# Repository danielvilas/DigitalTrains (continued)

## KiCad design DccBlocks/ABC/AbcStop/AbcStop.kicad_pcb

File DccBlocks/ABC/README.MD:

# ABC Stop Signal Generator
Generator of Lenz's async signal to stop a loco

Subprojects
* __[AbcSimulation](AbcSimulation)__:Simulation Circuits to Test
* __[AbcStop](AbcStop)__: Stop Circuit generator with Mosfet ByPass
* __[AbcTestBoard](AbcTestBoard)__: Test Board for the checking the Mosfets circuits

## TODO
- Hardware
  - [x] Join Test and Stop
  - [] Diode Documentation
  - [] Add a DCC decoder
  - [] DCC self Powered (from DCC)
  - [] Version no Opto
- Software
  - [] On/Off
  - [] Slow?
  - [] Study PIC, RP2040,...

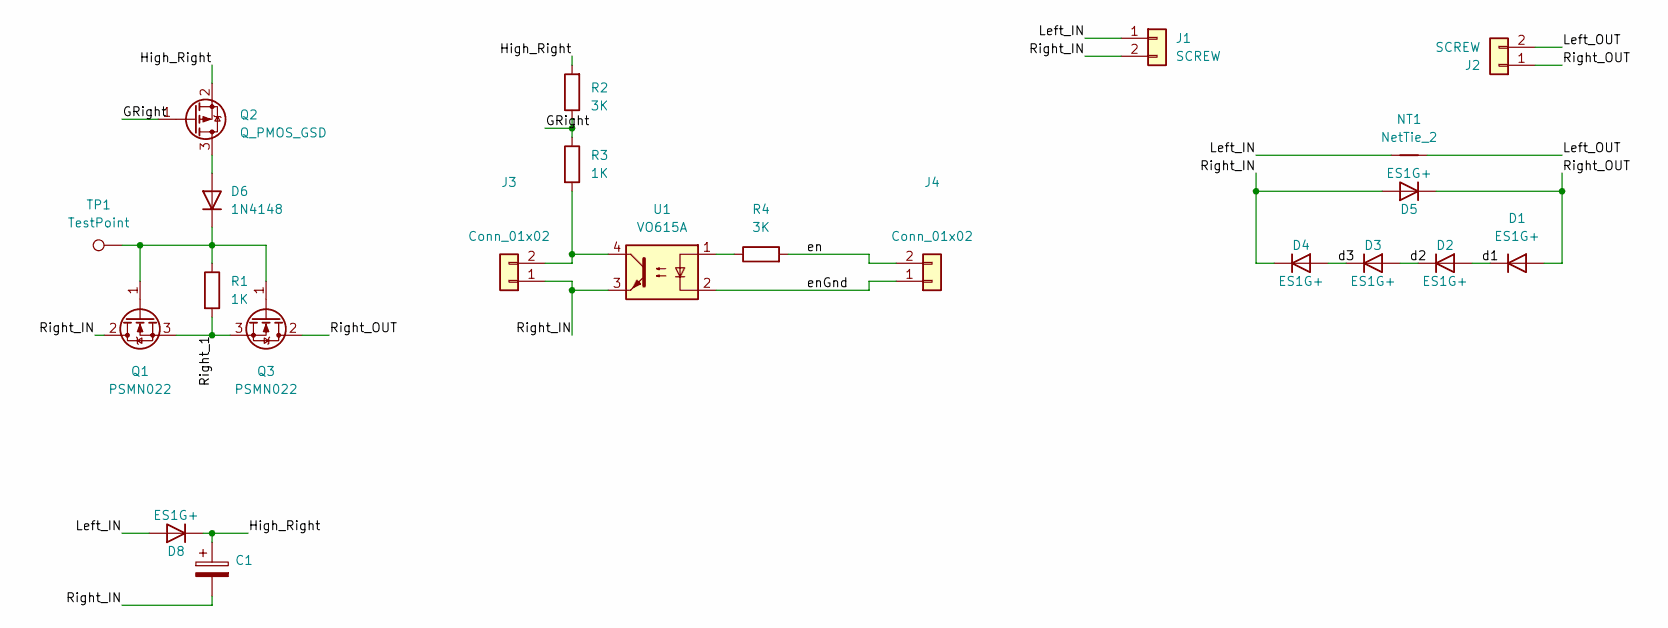
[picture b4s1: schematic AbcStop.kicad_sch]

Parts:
C1: 4.7uF; CP_Elec_4x5.4
D1, D2, D3, D4, D5, D8: ES1G+; D_SMA
D6: 1N4148; D_SOD-323
J1, J2: SCREW; TerminalBlock_Phoenix_PT-1,5-2-3.5-H_1x02_P3.50mm_Horizontal
J3, J4: Conn_01x02; PinHeader_1x02_P2.54mm_Vertical
NT1: NetTie_2; NetTie-2_SMD_Pad2.0mm
Q1, Q3: PSMN022; sot404
Q2: Q_PMOS_GSD; SOT-23
R1, R3: 1K; R_1206_3216Metric_Pad1.30x1.75mm_HandSolder
R2, R4: 3K; R_1206_3216Metric_Pad1.30x1.75mm_HandSolder
TP1: TestPoint; TestPoint_Pad_D1.5mm
U1: VO615A; SMDIP-4_W9.53mm

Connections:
/GRight: Q2.1 (G), R2.1, R3.1
/High_Right: C1.1, D8.1 (K), Q2.2 (S), R2.2
/Left_IN: D8.2 (A), J1.1, NT1.1
/Left_OUT: J2.2, NT1.2
/Right_1: Q1.3 (S), Q3.3 (S), R1.2
/Right_IN: C1.2, D4.1 (K), D5.2 (A), J1.2, J3.1, Q1.2 (D), U1.3
/Right_OUT: D1.2 (A), D5.1 (K), J2.1, Q3.2 (D)
/d1: D1.1 (K), D2.2 (A)
/d2: D2.1 (K), D3.2 (A)
/d3: D3.1 (K), D4.2 (A)
/en: J4.2, R4.2
/enGnd: J4.1, U1.2
unnamed: D6.2 (A), Q2.3 (D)
unnamed: D6.1 (K), Q1.1 (G), Q3.1 (G), R1.1, TP1.1
unnamed: J3.2, R3.2, U1.4
unnamed: R4.1, U1.1

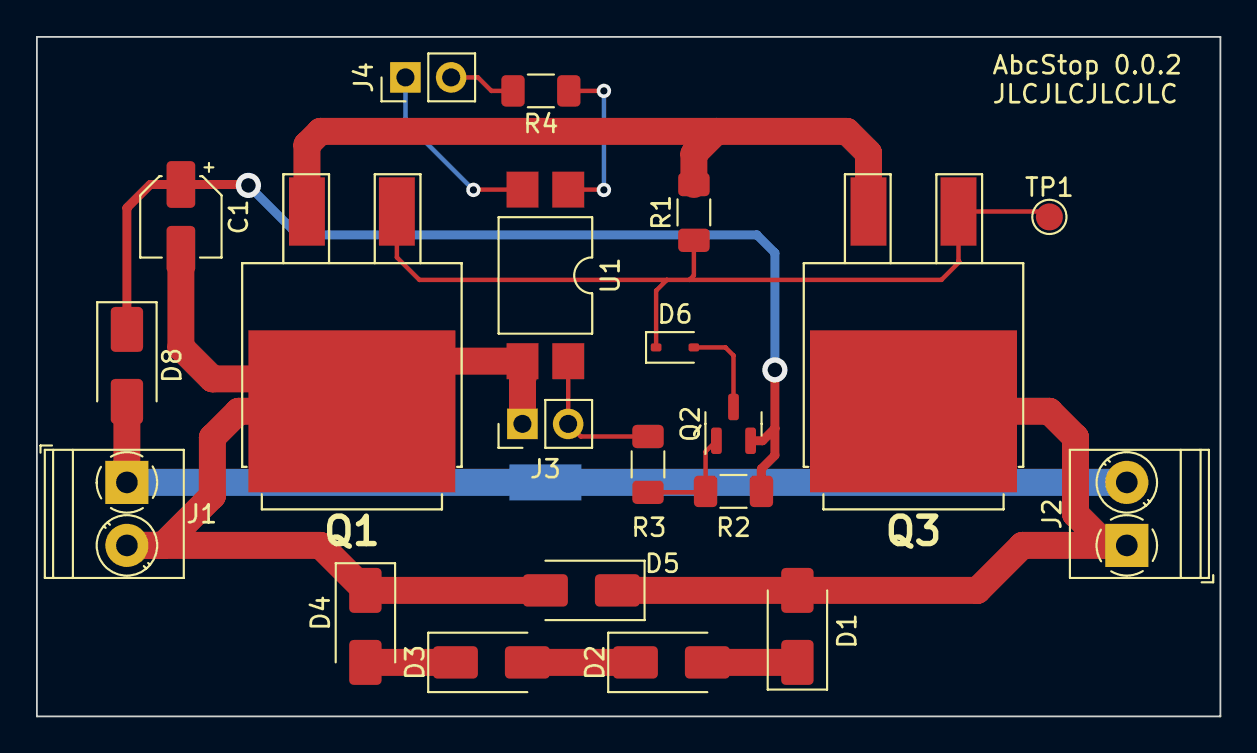
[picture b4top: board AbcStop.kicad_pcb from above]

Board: 2 copper layers, 65.8 x 37.8 mm, 22 parts (1 on the bottom side), 16 nets.

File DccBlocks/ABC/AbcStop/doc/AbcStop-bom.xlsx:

|  | Bill of Materials
 |  | Schematic: | AbcStop | Component Groups: | 10
 |  | Variant: | default | Component Count: | 20 (16 SMD/ 4 THT)
 |  | Revision: | 0.0.2 | Fitted Components: | 20 (16 SMD/ 4 THT)
 |  | Date: | 2023-06-01 | Number of PCBs: | 1
 |  | KiCad Version: | 7.0.5.1-1-g8f565ef7f0-dirty-deb11 | Total Components: | 20
Row | Description | Part | References | Value | Footprint | Quantity Per PCB | Status | Datasheet | Sim.Device | Sim.Pins
1 | Polarized capacitor | C_Polarized | C1 | 4.7uF | CP_Elec_4x5.4 | 1 |  | ~
2 | 100V 0.15A standard switching diode, DO-35 | 1N4148 | D6 | 1N4148 | D_SOD-323 | 1 |  | https://assets.nexperia.com/documents/data-sheet/1N4148_1N4448.pdf | D | 1=K 2=A
3 | Diode | D | D1 D2 D3 D4 D5 D8 | ES1G+ | D_SMA | 6 |  | ~ | D | 1=K 2=A
4 | Generic connector, single row, 01x02, script generated (kicad-library-utils/sch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 | Conn_01x02 | J3 J4 | Conn_01x02 | PinHeader_1x02_P2.54mm_Vertical | 2 |  | ~
5 | Generic connector, single row, 01x02, script generated (kicad-library-utils/sch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 | Conn_01x02 | J1 J2 | SCREW | TerminalBlock_Phoenix_PT-1,5-2-3.5-H_1x02_P3.50mm_Horizontal | 2 |  | ~
6 | N-MOSFET transistor, gate/drain/source | Q_NMOS_GDS | Q1 Q3 | PSMN022 | sot404 | 2 |  | ~
7 | P-MOSFET transistor, gate/source/drain | Q_PMOS_GSD | Q2 | Q_PMOS_GSD | SOT-23 | 1 |  | ~
8 | Resistor | R | R1 R3 | 1K | R_1206_3216Metric_Pad1.30x1.75mm_HandSolder | 2 |  | ~
9 | Resistor | R | R2 R4 | 3K | R_1206_3216Metric_Pad1.30x1.75mm_HandSolder | 2 |  | ~
10 | DC Optocoupler, Vce 70V, CTR 50-600% @ 5mA, Viso 5000Vrms, DIP4 | VO615A | U1 | VO615A | SMDIP-4_W9.53mm | 1 |  | http://www.vishay.com/docs/81753/vo615a.pdf

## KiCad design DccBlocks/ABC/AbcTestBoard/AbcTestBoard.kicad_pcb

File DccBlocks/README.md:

# DCC Blocks
Blocks to build a DCC sytem.

## Status
Stall. With the current version it is possible to run trains. Needs an update for the silk screens and for DCC++EX

## Subprojects
* __[ABC](ABC)__: Automatic Brake Control signal generator, 
* __[BoostModule](BoostModule)__: Motorshield adapted for DCC++
* __[DccModule](DccModule)__: MainController, arduino with some RGB leds and connectors for DCC++ (BoostModule)
* __[Detection](Detection)__: Small Boards to detect ocuppancy on tracks by current.
* __[IndicartorLeds](IndicartorLeds)__: Board to hold a few leds on a small pcb, to use in mimic panels or similar.

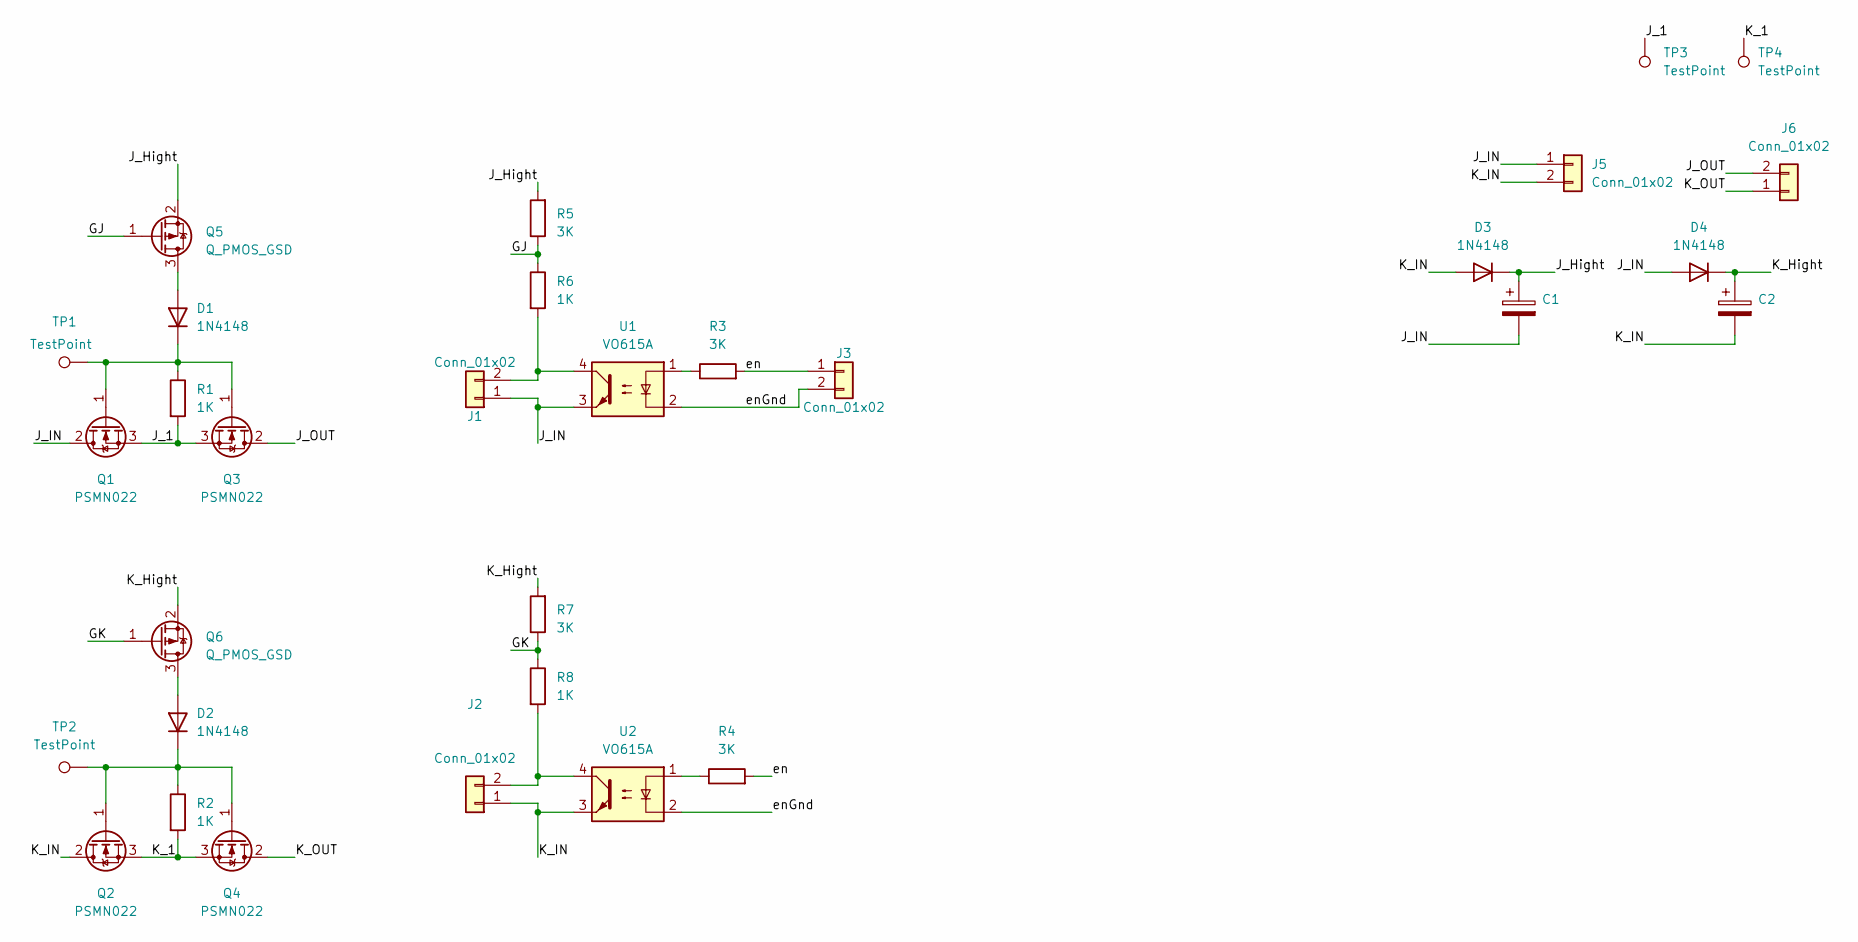
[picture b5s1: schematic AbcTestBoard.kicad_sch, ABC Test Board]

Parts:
C1, C2: 4.7uF; CP_Elec_4x5.4
D1, D2, D3, D4: 1N4148; D_SOD-323
J1, J2, J3: Conn_01x02; PinHeader_1x02_P2.54mm_Vertical
J5, J6: Conn_01x02; TerminalBlock_Phoenix_PT-1,5-2-3.5-H_1x02_P3.50mm_Horizontal
Q1, Q2, Q3, Q4: PSMN022; sot404
Q5, Q6: Q_PMOS_GSD; SOT-23
R1, R2, R6, R8: 1K; R_1206_3216Metric_Pad1.30x1.75mm_HandSolder
R3, R4, R5, R7: 3K; R_1206_3216Metric_Pad1.30x1.75mm_HandSolder
TP1, TP2, TP3, TP4: TestPoint; TestPoint_Pad_D1.5mm
U1, U2: VO615A; SMDIP-4_W9.53mm

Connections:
/GJ: Q5.1 (G), R5.1, R6.1
/GK: Q6.1 (G), R7.1, R8.1
/J_1: Q1.3 (S), Q3.3 (S), R1.2, TP3.1
/J_Hight: C1.1, D3.1 (K), Q5.2 (S), R5.2
/J_IN: C1.2, D4.2 (A), J1.1, J5.1, Q1.2 (D), U1.3
/J_OUT: J6.2, Q3.2 (D)
/K_1: Q2.3 (S), Q4.3 (S), R2.2, TP4.1
/K_Hight: C2.1, D4.1 (K), Q6.2 (S), R7.2
/K_IN: C2.2, D3.2 (A), J2.1, J5.2, Q2.2 (D), U2.3
/K_OUT: J6.1, Q4.2 (D)
/en: J3.1, R3.2, R4.2
/enGnd: J3.2, U1.2, U2.2
unnamed: D1.2 (A), Q5.3 (D)
unnamed: D1.1 (K), Q1.1 (G), Q3.1 (G), R1.1, TP1.1
unnamed: D2.2 (A), Q6.3 (D)
unnamed: D2.1 (K), Q2.1 (G), Q4.1 (G), R2.1, TP2.1
unnamed: J1.2, R6.2, U1.4
unnamed: J2.2, R8.2, U2.4
unnamed: R3.1, U1.1
unnamed: R4.1, U2.1

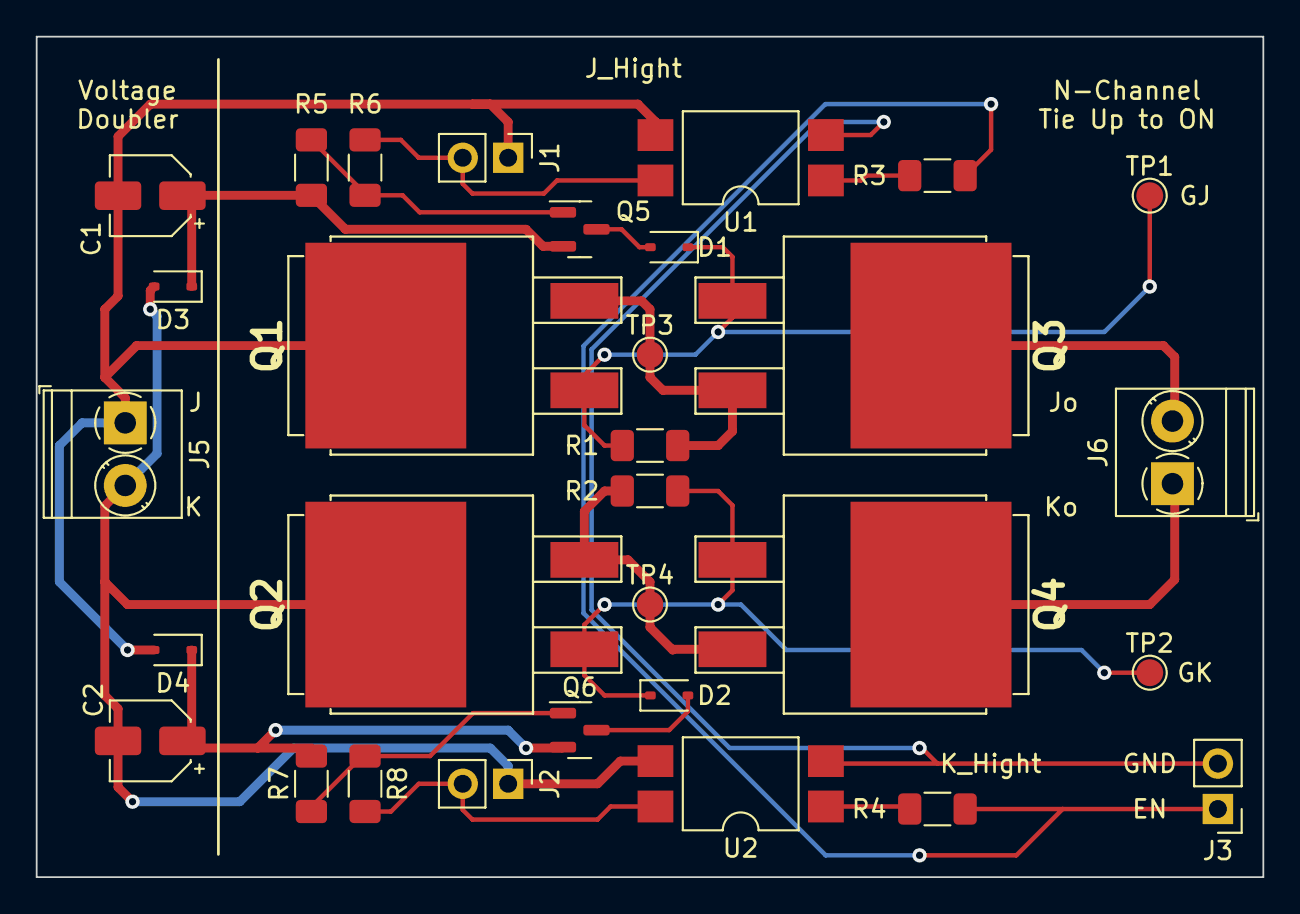
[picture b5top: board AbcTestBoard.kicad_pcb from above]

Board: 2 copper layers, 68.6 x 47.0 mm, 31 parts (0 on the bottom side), 20 nets.

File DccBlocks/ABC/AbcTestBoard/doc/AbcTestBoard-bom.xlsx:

|  | Bill of Materials
 |  | Schematic: | AbcTestBoard | Component Groups: | 9
 |  | Variant: | default | Component Count: | 27 (22 SMD/ 5 THT)
 |  | Revision: |  | Fitted Components: | 27 (22 SMD/ 5 THT)
 |  | Date: | 2023-05-31_17-01-39 | Number of PCBs: | 1
 |  | KiCad Version: | 7.0.5.1-1-g8f565ef7f0-dirty-deb11 | Total Components: | 27
Row | Description | Part | References | Value | Footprint | Quantity Per PCB | Status | Datasheet | Sim.Device | Sim.Pins
1 | Polarized capacitor | C_Polarized | C1 C2 | 4.7uF | CP_Elec_4x5.4 | 2 |  | ~
2 | 100V 0.15A standard switching diode, DO-35 | 1N4148 | D1 D2 D3 D4 | 1N4148 | D_SOD-323 | 4 |  | https://assets.nexperia.com/documents/data-sheet/1N4148_1N4448.pdf | D | 1=K 2=A
3 | Generic connector, single row, 01x02, script generated (kicad-library-utils/sch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 | Conn_01x02 | J1 J2 J3 | Conn_01x02 | PinHeader_1x02_P2.54mm_Vertical | 3 |  | ~
4 | Generic connector, single row, 01x02, script generated (kicad-library-utils/sch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 | Conn_01x02 | J5 J6 | Conn_01x02 | TerminalBlock_Phoenix_PT-1,5-2-3.5-H_1x02_P3.50mm_Horizontal | 2 |  | ~
5 | N-MOSFET transistor, gate/drain/source | Q_NMOS_GDS | Q1 Q2 Q3 Q4 | PSMN022 | sot404 | 4 |  | ~
6 | P-MOSFET transistor, gate/source/drain | Q_PMOS_GSD | Q5 Q6 | Q_PMOS_GSD | SOT-23 | 2 |  | ~
7 | Resistor | R | R1 R2 R6 R8 | 1K | R_1206_3216Metric_Pad1.30x1.75mm_HandSolder | 4 |  | ~
8 | Resistor | R | R3 R4 R5 R7 | 3K | R_1206_3216Metric_Pad1.30x1.75mm_HandSolder | 4 |  | ~
9 | DC Optocoupler, Vce 70V, CTR 50-600% @ 5mA, Viso 5000Vrms, DIP4 | VO615A | U1 U2 | VO615A | SMDIP-4_W9.53mm | 2 |  | http://www.vishay.com/docs/81753/vo615a.pdf

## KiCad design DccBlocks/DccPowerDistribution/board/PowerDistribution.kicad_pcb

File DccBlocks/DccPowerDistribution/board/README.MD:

# Dcc Power Distribution
This is a board to get power from a 12V DC or DCC bus, outputs the input as DC (12V or 14V from DCC), 5V and 3.3V. Includes an DCC interface to interactuate with the layout if needed.

Intended to use inside a module for its own power ussage. 

## Desired Specs Status
* [x] Power selection from DCC or External 12V supply
  * [ ] A switch is OK
  * [x] Auto selecction if possible
* [x] Power Rails
  * [x] 12V Vin
  * [x] 5V for accesories (servo, rele), Buck
  * [x] 3.3V for MCU If needed, LDO

## Power Design
From the dcc turnout we want **1 AMP output** wiht nominal output of **500mA**, enought for a Servo in stall and some accesories.

Degub led consumption with provided Resistences:

|Led|Color used| VLed| Current | V Mesured| VR | R|
|---|---|---|---|---|---|---|
|D4 Vdrive|White|2.92V| 12.9 mA|14.54V|11.62V|900|
|D5 5V|Blue|2.89V| 10.4 mA|2.08V|4.97V|200|
|D6 3.3V|Light Blue|2.75V| 5.6 mA|0.56V|11.62V|100|

## ChangeLog
### v1.0.0-RC1
* [x] Initial Version from Dcc Turnout Decoder
* [x] Change project name with kicad project rename

### V1.0.0-RC2
* [x] Correct Silk Version (0.3.0 -> 1.0.0-RC2)
* [x] Added Bulk Capacitance on Vdrive
* [x] Changed bridge to schottky one
* [x] Correct ECR (Net Ties - names)

### V1.0.0-RC3
* [X] Heat Analisys
* [X]  Check Position of JP3 And JP4
* [X]  Isolate Deco GND
* [ ] Add Test Points
  * [X] Voltage Main (GND, Vdrive,+5V, +3.3V)
  * [X] Voltage Others (VDcc,Gnd_Dcc, VDecoder,GND_Deco)
  * [X] Gate-Source Q4 (VDcc Blocker)
  * [X] For Debug leds
* [X] See U? on the silk (usefull for doc)
* [X] Change Power Diodes 
* [X] Change Bridge Rectifier To power Diodes
* [X] Change PMos (blocker) for IRLML9301TRPBF

### V1.0.0-RC4
* [ ] Find another D valid for D13/D2
* [ ] Find another D valid for D1/D8
* [ ] Rename components based on page num 
* [ ] Check CC only & DCC at the same time
* [ ] Add auto selection Debug Leds
* [ ] Add Pi Filter to VDrive

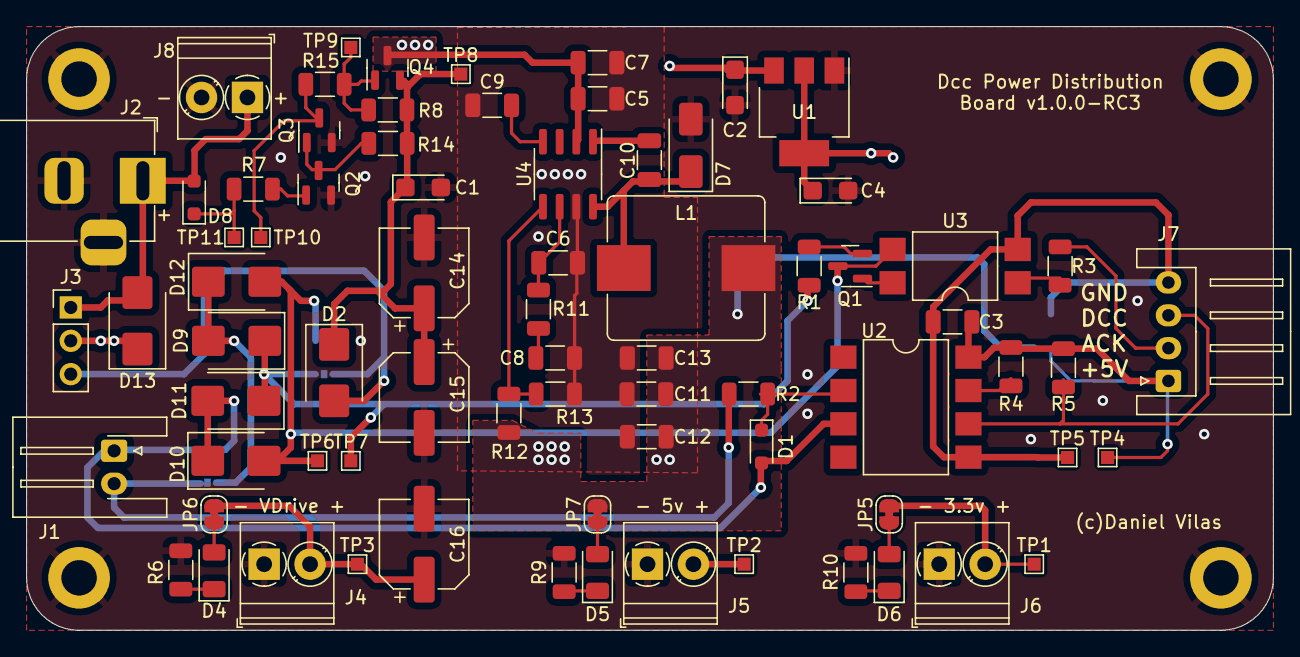
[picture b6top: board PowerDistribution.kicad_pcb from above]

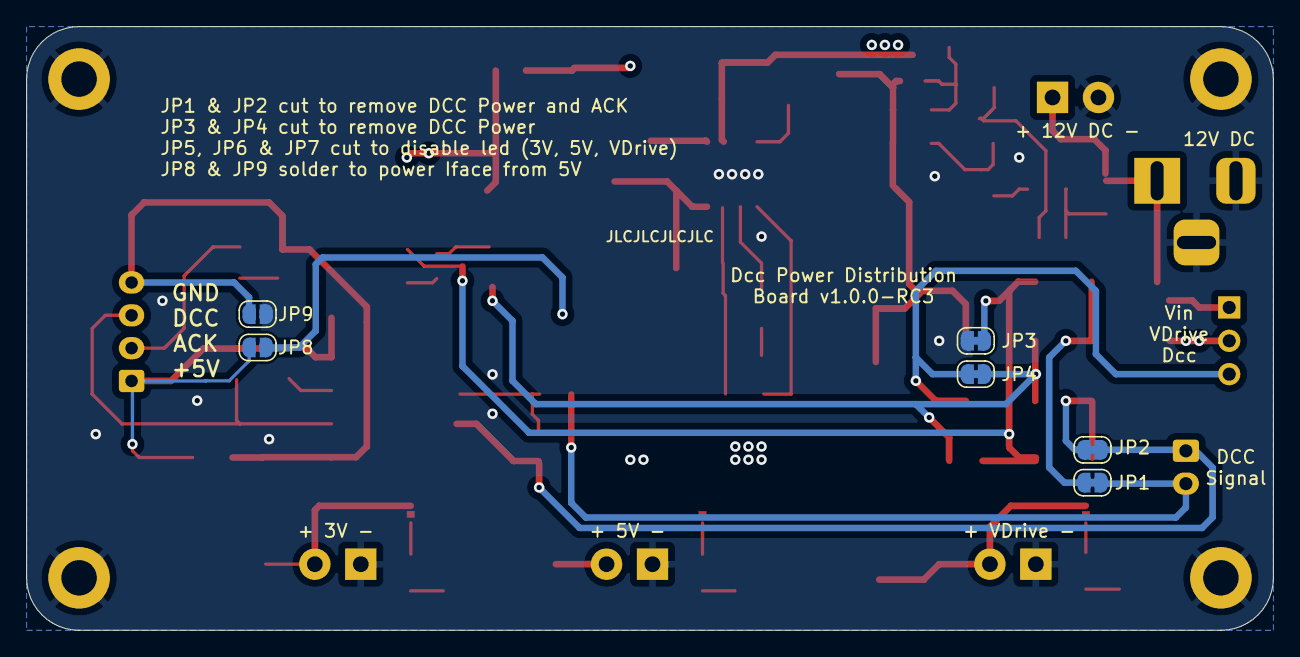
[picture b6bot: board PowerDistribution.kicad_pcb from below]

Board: 4 copper layers, 95.0 x 46.0 mm, 84 parts (6 on the bottom side), 39 nets.

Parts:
C1, C2, C4: 10uf; CP_EIA-3216-18_Kemet-A
C3, C5, C7, C11, C12, C13: 10uf; C_1206_3216Metric
C6: 10pf; C_1206_3216Metric
C8: 5.6nf; C_1206_3216Metric
C9: 8.2nf; C_1206_3216Metric
C10: 100nf; C_1206_3216Metric
C14, C15, C16: 100uf; CP_Elec_6.3x7.7
D1, D8: 1N4148; D_SOD-323_HandSoldering
D2, D9, D10, D11, D12, D13: SK34B; D_SMB
D4, D5, D6: LED; LED_1206_3216Metric
D7: SS24A+; D_SMA
H1, H2, H3, H4: MountingHole_Pad; MountingHole_2.7mm_M2.5_DIN965_Pad
J1: JST_01x02; JST_XH_S2B-XH-A-1_1x02_P2.50mm_Horizontal
J2: DcJackSW; BarrelJack_Horizontal
J3: Pin_01x03; PinHeader_1x03_P2.54mm_Vertical
J4, J5, J6: Screw_01x02_blue; TerminalBlock_Phoenix_PT-1,5-2-3.5-H_1x02_P3.50mm_Horizontal
J7: JST_01x04; JST_XH_S4B-XH-A_1x04_P2.50mm_Horizontal
J8: Screw_01x02_Black; TerminalBlock_Phoenix_PT-1,5-2-3.5-H_1x02_P3.50mm_Horizontal
JP1, JP2, JP3, JP4: Jumper_NC; SolderJumper-2_P1.3mm_Bridged_RoundedPad1.0x1.5mm
JP5, JP6, JP7: Jumper_2_Bridged; SolderJumper-2_P1.3mm_Bridged_RoundedPad1.0x1.5mm
JP8, JP9: SolderJumper_2_Open; SolderJumper-2_P1.3mm_Open_RoundedPad1.0x1.5mm
L1: 22uH; L_Bourns_SRP1035
Q1: BC857; SOT-23
Q2: BC817; SOT-23
Q3: 2N7002; SOT-23
Q4: BSS308; SOT-23
R1, R10: 100; R_1206_3216Metric
R2: 3k; R_1206_3216Metric
R3: 1K; R_1206_3216Metric
R4, R5: 10K; R_1206_3216Metric
R6: 900; R_1206_3216Metric
R7, R8, R14, R15: 100K; R_1206_3216Metric
R9: 200; R_1206_3216Metric
R11: 5.62K; R_1206_3216Metric
R12: 10.2K; R_1206_3216Metric
R13: 1.96K; R_1206_3216Metric
TP1, TP2, TP3, TP4, TP5, TP6, TP7, TP8, TP9, TP10, TP11: TestPoint; TestPoint_Pad_1.0x1.0mm
U1: AMS1117-3.3; SOT-223-3_TabPin2
U2: 6N137S1; SMDIP-8_W9.53mm
U3: PC817; SMDIP-4_W9.53mm
U4: TPS54331D; SOIC-8_3.9x4.9mm_P1.27mm

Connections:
+3.3V: C4.1, J6.2, JP5.2 (B), TP1.1, U1.2 (VO)
+5V: C2.1, C11.1, C12.1, C13.1, J5.2, JP7.2 (B), JP8.1 (A), L1.2, R12.1, TP2.1, U1.3 (VI)
/5V_iface: C3.1, J7.1, JP8.2 (B), R4.2, R5.2, TP4.1, U2.8 (VCC)
/Dcc Interface/DccP+: D9.1 (K), D11.1 (K), JP4.1 (A), R1.2, TP7.1
/Dcc Interface/DccP-: D10.2 (A), D12.2 (A), JP3.1 (A), Q1.3 (C), TP6.1, U3.3
/Dcc Interface/J: J1.2, JP1.2 (B), R2.2
/Dcc Interface/J_ACK: D9.2 (A), D12.1 (K), JP1.1 (A)
/Dcc Interface/K: D1.2 (A), J1.1, JP2.2 (B), U2.3 (C)
/Dcc Interface/K_ACK: D10.1 (K), D11.2 (A), JP2.1 (A)
/GND_iface: C3.2, J7.4, JP9.2 (B), TP5.1, U2.5 (GND), U3.2
/Power Distribution/DccVin: D2.2 (A), J3.3, JP4.2 (B)
/Power Distribution/Vin: D8.2 (A), D13.2 (A), J2.1, J3.1, J8.1
/Power Distribution/_BOOT: C10.1, U4.1 (BOOT)
/Power Distribution/_DccVinP: C1.1, C14.1, C15.1, D2.1 (K), Q4.2 (S), R8.1, R14.1, TP8.1
/Power Distribution/_PH: C10.2, D7.1 (K), L1.1, U4.8 (PH)
/_ack: J7.2, R3.1
/_dcc: J7.3, R5.1, U2.6 (VO)
GND: C1.2, C2.2, C4.2, C5.2, C6.2, C7.2, C8.2, C9.2, C11.2, C12.2, C13.2, C14.2, C15.2, C16.2, D7.2 (A), H1.1, H2.1, H3.1, H4.1, J2.2, J2.3, J4.1, J5.1, J6.1, J8.2, JP3.2 (B), JP9.1 (A), Q2.2 (E), Q3.2 (S), R6.2, R9.2, R10.2, R13.2, U1.1 (GND), U4.7 (GND)
unnamed: C8.1, R11.2
unnamed: D1.1 (K), R2.1, U2.2 (A)
unnamed: D4.2 (A), JP6.1 (A)
unnamed: D4.1 (K), R6.1
unnamed: D5.2 (A), JP7.1 (A)
unnamed: D5.1 (K), R9.1
unnamed: D6.2 (A), JP5.1 (A)
unnamed: D6.1 (K), R10.1
unnamed: D8.1 (K), R7.2, TP11.1
unnamed: Q1.1 (B), U3.4
unnamed: Q1.2 (E), R1.1
unnamed: Q2.1 (B), R7.1
unnamed: Q2.3 (C), Q3.1 (G), R14.2
unnamed: Q3.3 (D), R15.1, TP10.1
unnamed: Q4.1 (G), R8.2, R15.2, TP9.1
unnamed: R3.2, U3.1
unnamed: R4.1, U2.7 (EN)
unnamed: C6.1, R11.1, U4.6 (COMP)
unnamed: C9.1, U4.4 (SS)
unnamed: R12.2, R13.1, U4.5 (VSENSE)
Vdrive: C5.1, C7.1, C16.1, D13.1 (K), J3.2, J4.2, JP6.2 (B), Q4.3 (D), TP3.1, U4.2 (VIN)

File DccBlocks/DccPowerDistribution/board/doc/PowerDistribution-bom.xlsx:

|  | Bill of Materials
 |  | Schematic: | PowerDistribution | Component Groups: | 40
 |  | Variant: | default | Component Count: | 67 (52 SMD/ 8 THT)
 |  | Revision: | v1.0.0-RC3 | Fitted Components: | 67 (52 SMD/ 8 THT)
 |  | Date: | 2023-04-30 | Number of PCBs: | 1
 |  | KiCad Version: | 7.0.2.1-36-g582732918d-dirty-deb11 | Total Components: | 67
Row | Description | Part | References | Value | Footprint | Quantity Per PCB | Status | Datasheet | Mouser# | MNF# | LCSC# | Farnell# | Tolerance | Sim.Device | Sim.Pins
1 | Unpolarized capacitor | C | C6 | 10pf | C_1206_3216Metric | 1 |  | ~ |  | 1206N100J500CT |  | 2497123
2 | Unpolarized capacitor | C | C8 | 5.6nf | C_1206_3216Metric | 1 |  | ~ |  | MC1206B562K500CT |  | 1759347
3 | Unpolarized capacitor | C | C9 | 8.2nf | C_1206_3216Metric | 1 |  | ~ |  | MC1206B822K500CT |  | 1759349
4 | Unpolarized capacitor | C | C10 | 100nf | C_1206_3216Metric | 1 |  | ~ |  | C1206C104M5RACTU |  | 2581103 | 1mO
5 | Polarized capacitor | C_Polarized | C1 C2 C4 | 10uf | CP_EIA-3216-18_Kemet-A | 3 |  | ~ | 80-T494A106M020 | T494A106M020AT | C7171 |  | ~
6 | Unpolarized capacitor | C | C5 C7 C11 C12 C13 | 10uf | C_1206_3216Metric | 5 |  | ~ | 187-CL31A106KPHNNNE | CL31A106KPHNNNE |  |  | 2mO
7 | Unpolarized capacitor | C | C3 | 10uf | C_1206_3216Metric | 1 |  | ~ |  |  | C15850 | 2803344 | ~
8 | Polarized capacitor | C_Polarized | C14 C15 C16 | 100uf | CP_Elec_6.3x7.7 | 3 |  | ~ |  | 865060445005
9 | 100V 0.15A standard switching diode, DO-35 | 1N4148 | D1 | 1N4148 | D_SOD-323_HandSoldering | 1 |  | https://assets.nexperia.com/documents/data-sheet/1N4148_1N4448.pdf | 833-1N4148WX-TP | 1N4148WX-TP | C2128
10 | Diode | D | D8 | 1N4148 | D_SOD-323_HandSoldering | 1 |  | ~ | 241-GS1510FLR100001 | GS1510FL_R1_00001 |  |  |  | D | 1=K 2=A
11 | Light emitting diode | LED | D4 D5 D6 | LED | LED_1206_3216Metric | 3 |  | ~
12 | Schottky diode, small symbol, filled shape | D_Schottky_Small_Filled | D2 D9 D10 D11 D12 D13 | SK34B | D_SMB | 6 |  | ~
13 | Schottky diode | D_Schottky | D7 | SS24A+ | D_SMA | 1 |  | ~ |  | SS24A+ |  | 2748189
14 | DC Barrel Jack with an internal switch | Barrel_Jack_Switch | J2 | DcJackSW | BarrelJack_Horizontal | 1 |  | ~ | 806-KLDX-0202-A | KLDX-0202-A
15 | Generic connector, single row, 01x02, script generated (kicad-library-utils/sch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 | Conn_01x02 | J1 | JST_01x02 | JST_XH_S2B-XH-A-1_1x02_P2.50mm_Horizontal | 1 |  | ~
16 | Generic connector, single row, 01x04, script generated (kicad-library-utils/sch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 | Conn_01x04 | J7 | JST_01x04 | JST_XH_S4B-XH-A_1x04_P2.50mm_Horizontal | 1 |  | ~
17 | Generic connector, single row, 01x03, script generated (kicad-library-utils/sch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 | Conn_01x03 | J3 | Pin_01x03 | PinHeader_1x03_P2.54mm_Vertical | 1 |  | ~ |  | 1776275-2 |  | 1098611
18 | Generic connector, single row, 01x02, script generated (kicad-library-utils/sch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 | Conn_01x02 | J8 | Screw_01x02_Black | TerminalBlock_Phoenix_PT-1,5-2-3.5-H_1x02_P3.50mm_Horizontal | 1 |  | ~ |  | CTB3051/2BK |  | 3882615
19 | Generic connector, single row, 01x02, script generated (kicad-library-utils/sch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 | Conn_01x02 | J4 J5 J6 | Screw_01x02_blue | TerminalBlock_Phoenix_PT-1,5-2-3.5-H_1x02_P3.50mm_Horizontal | 3 |  | ~ |  | 1776275-2 |  | 1098611
20 | Jumper, 2-pole, closed/bridged | Jumper_2_Bridged | JP5 JP6 JP7 | Jumper_2_Bridged | SolderJumper-2_P1.3mm_Bridged_RoundedPad1.0x1.5mm | 3 |  | ~
21 | Jumper, 2-pole, closed/bridged | Jumper_2_Bridged | JP1 JP2 JP3 JP4 | Jumper_NC | SolderJumper-2_P1.3mm_Bridged_RoundedPad1.0x1.5mm | 4 |  | ~
22 | Inductor | L | L1 | 22uH | L_Bourns_SRP1035 | 1 |  | ~ |  | SRP1038A-220M |  | 2434023 | 75mO
23 | 0.115A Id, 60V Vds, N-Channel MOSFET, SOT-23 | 2N7002 | Q3 | 2N7002 | SOT-23 | 1 |  | https://www.onsemi.com/pub/Collateral/NDS7002A-D.PDF
24 | 0.8A Ic, 45V Vce, NPN Transistor, SOT-23 | BC817 | Q2 | BC817 | SOT-23 | 1 |  | https://www.onsemi.com/pub/Collateral/BC818-D.pdf | 771-BC817-25-T/R | BC817-25,215
25 | PNP transistor, base/emitter/collector | Q_PNP_BEC | Q1 | BC857 | SOT-23 | 1 |  | http://www.fairchildsemi.com/ds/BC/BC557.pdf | 771-BC857C235 | BC857C,235 | C8326
26 | P-MOSFET transistor, gate/source/drain | Q_PMOS_GSD | Q4 | BSS308 | SOT-23 | 1 |  | ~ | 726-BSS308PEH6327 | BSS308PE H6327
27 | Resistor | R | R1 R10 | 100 | R_1206_3216Metric | 2 |  | ~ | 603-AC1206FR-10100RL | AC1206FR-10100RL | C17901
28 | Resistor | R | R9 | 200 | R_1206_3216Metric | 1 |  | ~ | 603-RC1206FR-07200RL | RC1206FR-07200RL
29 | Resistor | R | R6 | 900 | R_1206_3216Metric | 1 |  | ~ | 652-CR1206FX-9090ELF | CR1206-FX-9090ELF
30 | Resistor | R | R3 | 1K | R_1206_3216Metric | 1 |  | ~ | 652-CR1206FX-1001ELF | CR1206-FX-1001ELF | C17513
31 | Resistor | R | R13 | 1.96K | R_1206_3216Metric | 1 |  | ~ |  | ERJ8ENF1961V |  | 2307494
32 | Resistor | R | R2 | 3k | R_1206_3216Metric | 1 |  | ~ |  |  | C17661
33 | Resistor | R | R11 | 5.62K | R_1206_3216Metric | 1 |  | ~ |  | ERJ8ENF5621V |  | 2695169
34 | Resistor | R | R4 R5 | 10K | R_1206_3216Metric | 2 |  | ~ | 652-CR1206FX-1002ELF | CR1206-FX-1002ELF | C17414
35 | Resistor | R | R12 | 10.2K | R_1206_3216Metric | 1 |  | ~ |  | ERJ8ENF1022V |  | 2307301
36 | Resistor | R | R7 R8 R14 R15 | 100K | R_1206_3216Metric | 4 |  | ~
37 | Single High Speed LSTTL/TTL Compatible Optocoupler with enable, dV/dt 1000/us, 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 | 6N137 | U2 | 6N137S1 | SMDIP-8_W9.53mm | 1 |  | https://docs.broadcom.com/docs/AV02-0940EN | 512-6N137SDM | 6N137SDM | C110020
38 | 1A Low Dropout regulator, positive, 3.3V fixed output, SOT-223 | AMS1117-3.3 | U1 | AMS1117-3.3 | SOT-223-3_TabPin2 | 1 |  | http://www.advanced-monolithic.com/pdf/ds1117.pdf | 863-NCP1117LPST33T3G | NCP1117LPST33T3G | C6186
39 | DC Optocoupler, Vce 35V, CTR 50-300%, DIP-4 | PC817 | U3 | PC817 | SMDIP-4_W9.53mm | 1 |  | http://www.soselectronic.cz/a_info/resource/d/pc817.pdf | 852-PC817X2NIP1B | PC817X2NIP1B | C106900
40 | Buck Converter | TPS54331D | U4 | TPS54331D | SOIC-8_3.9x4.9mm_P1.27mm | 1 |  |  |  | TPS54331D |  | 1645383

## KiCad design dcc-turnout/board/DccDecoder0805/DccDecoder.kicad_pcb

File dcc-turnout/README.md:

# Dcc Turnout Controller
This board is a controller for moving a turnout using a servo.

## Status
Alive, current project

## Desired Specs
* 2 Outputs for LEDs Aspects, to Vin
* 1 Rele Ouput (5V or 0)
* UART for advanced configuration
* Configure Pins
  * CV Program to advanced CF
    * POM if possible
  * Config mode to capture dcc Address
  * Advanced config mode (2 packets, CV, value)
* Reset Button
* Programing port
  * Bootloader for uart if possible
  * if possible no BootX pins

> Power and Dcc interface is moved to [Power Distribution](../DccBlocks/DccPowerDistribution/)

From PowerDistribution:
* Power selection from DCC or External 12V supply
  * A switch is OK
  * Auto selecction if possible
* Power Rails
  * 12V Vin
  * 5V for accesories (servo, rele), Buck
  * 3.3V for MCU If needed, LDO

## Subprojects
* __[Devel Board](board/DccDev)__: Starting board, arduino factor. Finished.
* __[Board](board/DccDecoder)__: Final board, under development
* __[Board 0805](board/DccDecoder0805)__: The same board using 0805 components to PCBA
* __[ServoPmosModule](modules/ServoPmosModule)__: Small board to enable/disable power to a servo.
* __[Power Distribution](../DccBlocks/DccPowerDistribution/)__: Check this to see Power Distribution

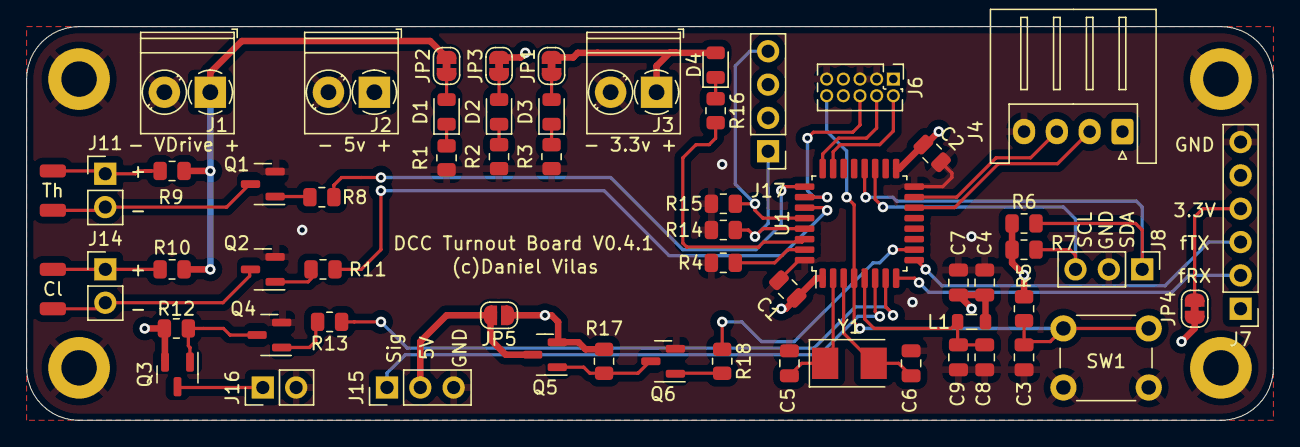
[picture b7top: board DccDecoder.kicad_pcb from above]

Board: 4 copper layers, 95.0 x 30.0 mm, 66 parts (0 on the bottom side), 46 nets.

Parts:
C1, C2, C3: 100nf; C_0805_2012Metric
C4, C8: 1uF; C_0805_2012Metric
C5, C6: 20pf; C_0805_2012Metric
C7, C9: 10nF; C_0805_2012Metric
D1, D2, D3, D4: LED; LED_0805_2012Metric
H1, H2, H3, H4: MountingHole_Pad; MountingHole_2.7mm_M2.5_DIN965_Pad
J1, J2, J3: Conn_01x02; TerminalBlock_Phoenix_PT-1,5-2-3.5-H_1x02_P3.50mm_Horizontal
J4: Conn_01x04; JST_XH_S4B-XH-A_1x04_P2.50mm_Horizontal
J6: Conn_02x05 Odd_Even; PinHeader_2x05_P1.27mm_Vertical
J7: Conn_01x06; PinHeader_1x06_P2.54mm_Vertical
J8, J15: Conn_01x03; PinHeader_1x03_P2.54mm_Vertical
J9, J10, J12, J13: Conn_01x01; SolderWirePad_1x01_SMD_1x2mm
J11, J14, J16: Conn_01x02; PinHeader_1x02_P2.54mm_Vertical
J17: Conn_01x04; PinHeader_1x04_P2.54mm_Vertical
JP1, JP2, JP3, JP4: Jumper_2_Bridged; SolderJumper-2_P1.3mm_Bridged_RoundedPad1.0x1.5mm
JP5: Jumper_2_Open; SolderJumper-2_P1.3mm_Open_RoundedPad1.0x1.5mm
L1: 10uH; L_0805_2012Metric
Q1, Q2, Q4, Q6: AO3400A; SOT-23
Q3, Q5: AO3401A; SOT-23
R1, R6, R7, R8, R9, R10, R11, R12, R13, R14, R15, R17, R18: 1K; R_0805_2012Metric
R2: 200; R_0805_2012Metric
R3, R16: 100; R_0805_2012Metric
R4, R5: 10K; R_0805_2012Metric
SW1: SW_Push; SW_PUSH_6mm
U1: STM32F030K6Tx; LQFP-32_7x7mm_P0.8mm
Y1: 8MHz; Crystal_SMD_5032-2Pin_5.0x3.2mm

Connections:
+3V3: C1.2, C2.2, C4.1, C7.1, D4.2 (A), J3.1, J6.1, J17.2, J17.3, JP1.2 (B), JP4.2 (B), L1.2, R5.1, R6.1, R7.1, U1.1 (VDD), U1.17 (VDD)
+5V: J2.1, J4.1, JP3.2 (B), JP5.1 (A), Q3.2 (S), Q5.2 (S), R12.2, R17.2
/CfgAdvanced: J17.4, R15.2, U1.28 (PB5)
/CfgBasic: J17.1, R14.2, U1.29 (PB6)
/CfgStatus: R16.2, U1.30 (PB7)
/ClosedLed: R11.1, U1.27 (PB4)
/F_RX: J7.2, U1.8 (PA2)
/F_TX: J7.3, U1.9 (PA3)
/F_Vcc: J7.4, JP4.1 (A)
/Out Puts/_ServoPwr: J15.2, JP5.2 (B), Q5.3 (D)
/ReleEn: R13.1, U1.7 (PA1)
/SCL: J8.3, R7.2, U1.19 (PA9)
/SDA: J8.1, R6.2, U1.20 (PA10)
/ServoEn: R18.1, U1.10 (PA4)
/ServoSig: J15.1, U1.6 (PA0)
/ThrownLed: R8.1, U1.25 (PA15)
/_ack: J4.2, U1.14 (PB0)
/_dcc: J4.3, U1.15 (PB1)
/uC 030K6/BOOT0: R4.1, U1.31 (BOOT0)
/uC 030K6/OSC_IN: C5.1, U1.2 (PF0), Y1.1
/uC 030K6/OSC_OUT: C6.1, U1.3 (PF1), Y1.2
/uC 030K6/PA13: J6.2, U1.23 (PA13)
/uC 030K6/PA14: J6.4, U1.24 (PA14)
/uC 030K6/PB3: J6.6, U1.26 (PB3)
/uC 030K6/RST: C3.1, J6.10, R5.2, SW1.1, U1.4 (NRST)
/uC 030K6/_VDDA: C8.1, C9.1, L1.1, U1.5 (VDDA)
GND: C1.1, C2.1, C3.2, C4.2, C5.2, C6.2, C7.2, C8.2, C9.2, H1.1, H2.1, H3.1, H4.1, J1.2, J2.2, J3.2, J4.4, J6.3, J6.5, J6.9, J7.6, J8.2, J15.3, J16.2, Q1.2 (S), Q2.2 (S), Q4.2 (S), Q6.2 (S), R1.2, R2.2, R3.2, R4.2, R14.1, R15.1, SW1.2, U1.16 (VSS), U1.32 (VSS)
unnamed: D1.1 (K), R1.1
unnamed: D1.2 (A), JP2.1 (A)
unnamed: D2.1 (K), R2.1
unnamed: D2.2 (A), JP3.1 (A)
unnamed: D3.1 (K), R3.1
unnamed: D3.2 (A), JP1.1 (A)
unnamed: D4.1 (K), R16.1
unnamed: J10.1, J11.2, Q1.3 (D)
unnamed: J9.1, J11.1, R9.1
unnamed: J12.1, J14.1, R10.1
unnamed: J13.1, J14.2, Q2.3 (D)
unnamed: J16.1, Q3.3 (D)
unnamed: Q1.1 (G), R8.2
unnamed: Q2.1 (G), R11.2
unnamed: Q3.1 (G), Q4.3 (D), R12.1
unnamed: Q4.1 (G), R13.2
unnamed: Q5.1 (G), Q6.3 (D), R17.1
unnamed: Q6.1 (G), R18.2
Vdrive: J1.1, JP2.2 (B), R9.2, R10.2

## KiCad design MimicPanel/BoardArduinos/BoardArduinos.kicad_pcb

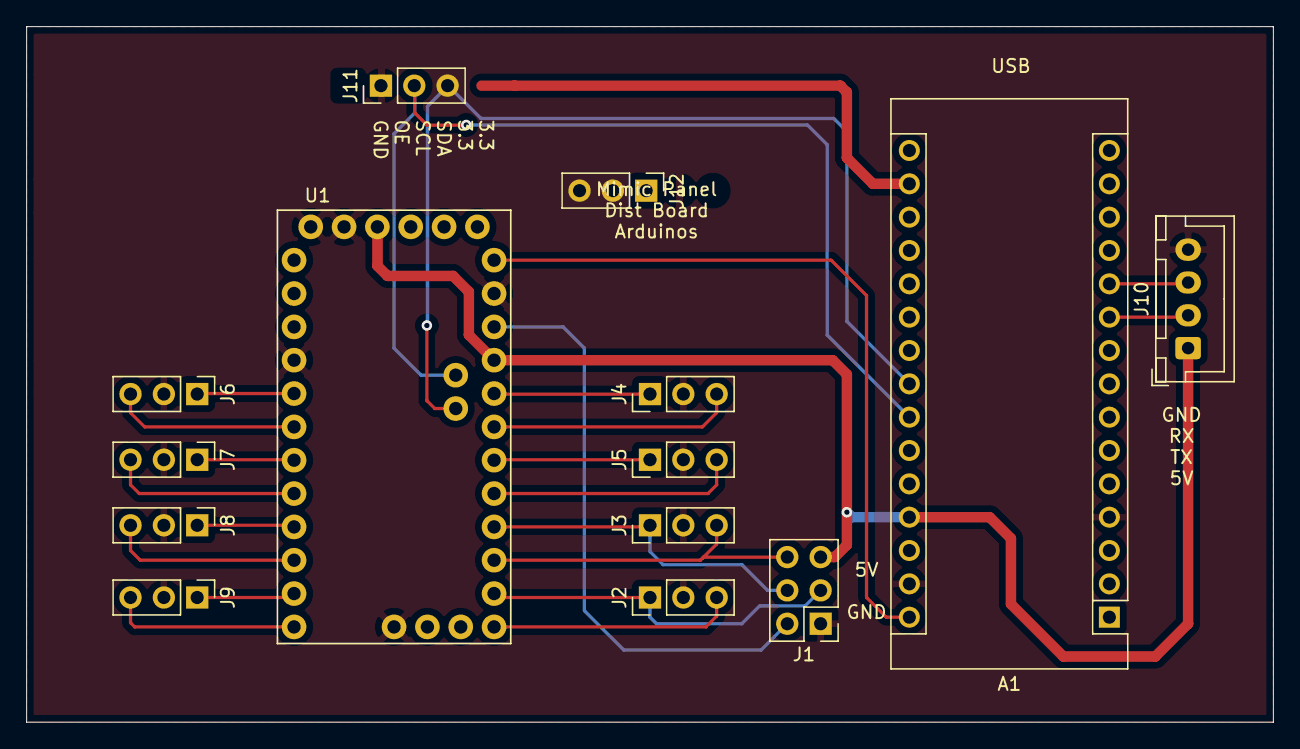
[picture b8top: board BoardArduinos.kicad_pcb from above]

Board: 2 copper layers, 95.0 x 53.0 mm, 14 parts (0 on the bottom side), 24 nets.

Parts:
A1: Arduino_Nano_v2.x; Arduino_Nano
J1: Conn_02x03_Odd_Even; PinHeader_2x03_P2.54mm_Vertical
J2, J3, J4, J5, J6, J7, J8, J9: Conn_01x03; PinHeader_1x03_P2.54mm_Vertical
J10: Conn_01x04; JST_XH_B4B-XH-A_1x04_P2.50mm_Vertical
J11, J12: Conn_01x06; PinHeader_1x03_P2.54mm_Vertical
U1: ARDUINO_PRO_MINI; MODULE_ARDUINO_PRO_MINI

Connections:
+5V: A1.27, J1.5, J10.1, J12.1, U1.JP1_4, U1.JP6_4
/DC_1: J6.3, U1.JP7_7
/DC_2: J7.3, U1.JP7_5
/DC_3: J8.1, U1.JP7_4
/DC_4: J9.3, U1.JP7_1
/DC_5: J2.3, U1.JP6_12
/DC_6: J1.6, J3.3, U1.JP6_10
/DC_7: J4.3, U1.JP6_6
/DC_8: J5.3, U1.JP6_8
/DT_1: J6.1, U1.JP7_8
/DT_2: J7.1, U1.JP7_6
/DT_3: J8.3, U1.JP7_3
/DT_4: J9.1, U1.JP7_2
/DT_5: J1.3, J2.1, U1.JP6_11
/DT_6: J1.4, J3.1, U1.JP6_9
/DT_7: J4.1, U1.JP6_5
/DT_8: J5.1, U1.JP6_7
/Loco_Rx: A1.11, J10.3
/Loco_TX: A1.10, J10.2
/Rst_Mini: J1.2, U1.JP6_3
/SCL: A1.24, J11.1, U1.JP2_2
/SDA: A1.23, J11.3, U1.JP2_1
GND: A1.4, A1.29, J1.1, J2.2, J3.2, J4.2, J5.2, J6.2, J7.2, J8.2, J9.2, J10.4, J11.2, J12.2, U1.JP1_5, U1.JP1_6, U1.JP3_3, U1.JP6_2, U1.JP7_9
VBUS: A1.30, U1.JP6_1
